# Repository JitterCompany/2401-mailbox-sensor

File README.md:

# Prototype voor brievenbus sensor

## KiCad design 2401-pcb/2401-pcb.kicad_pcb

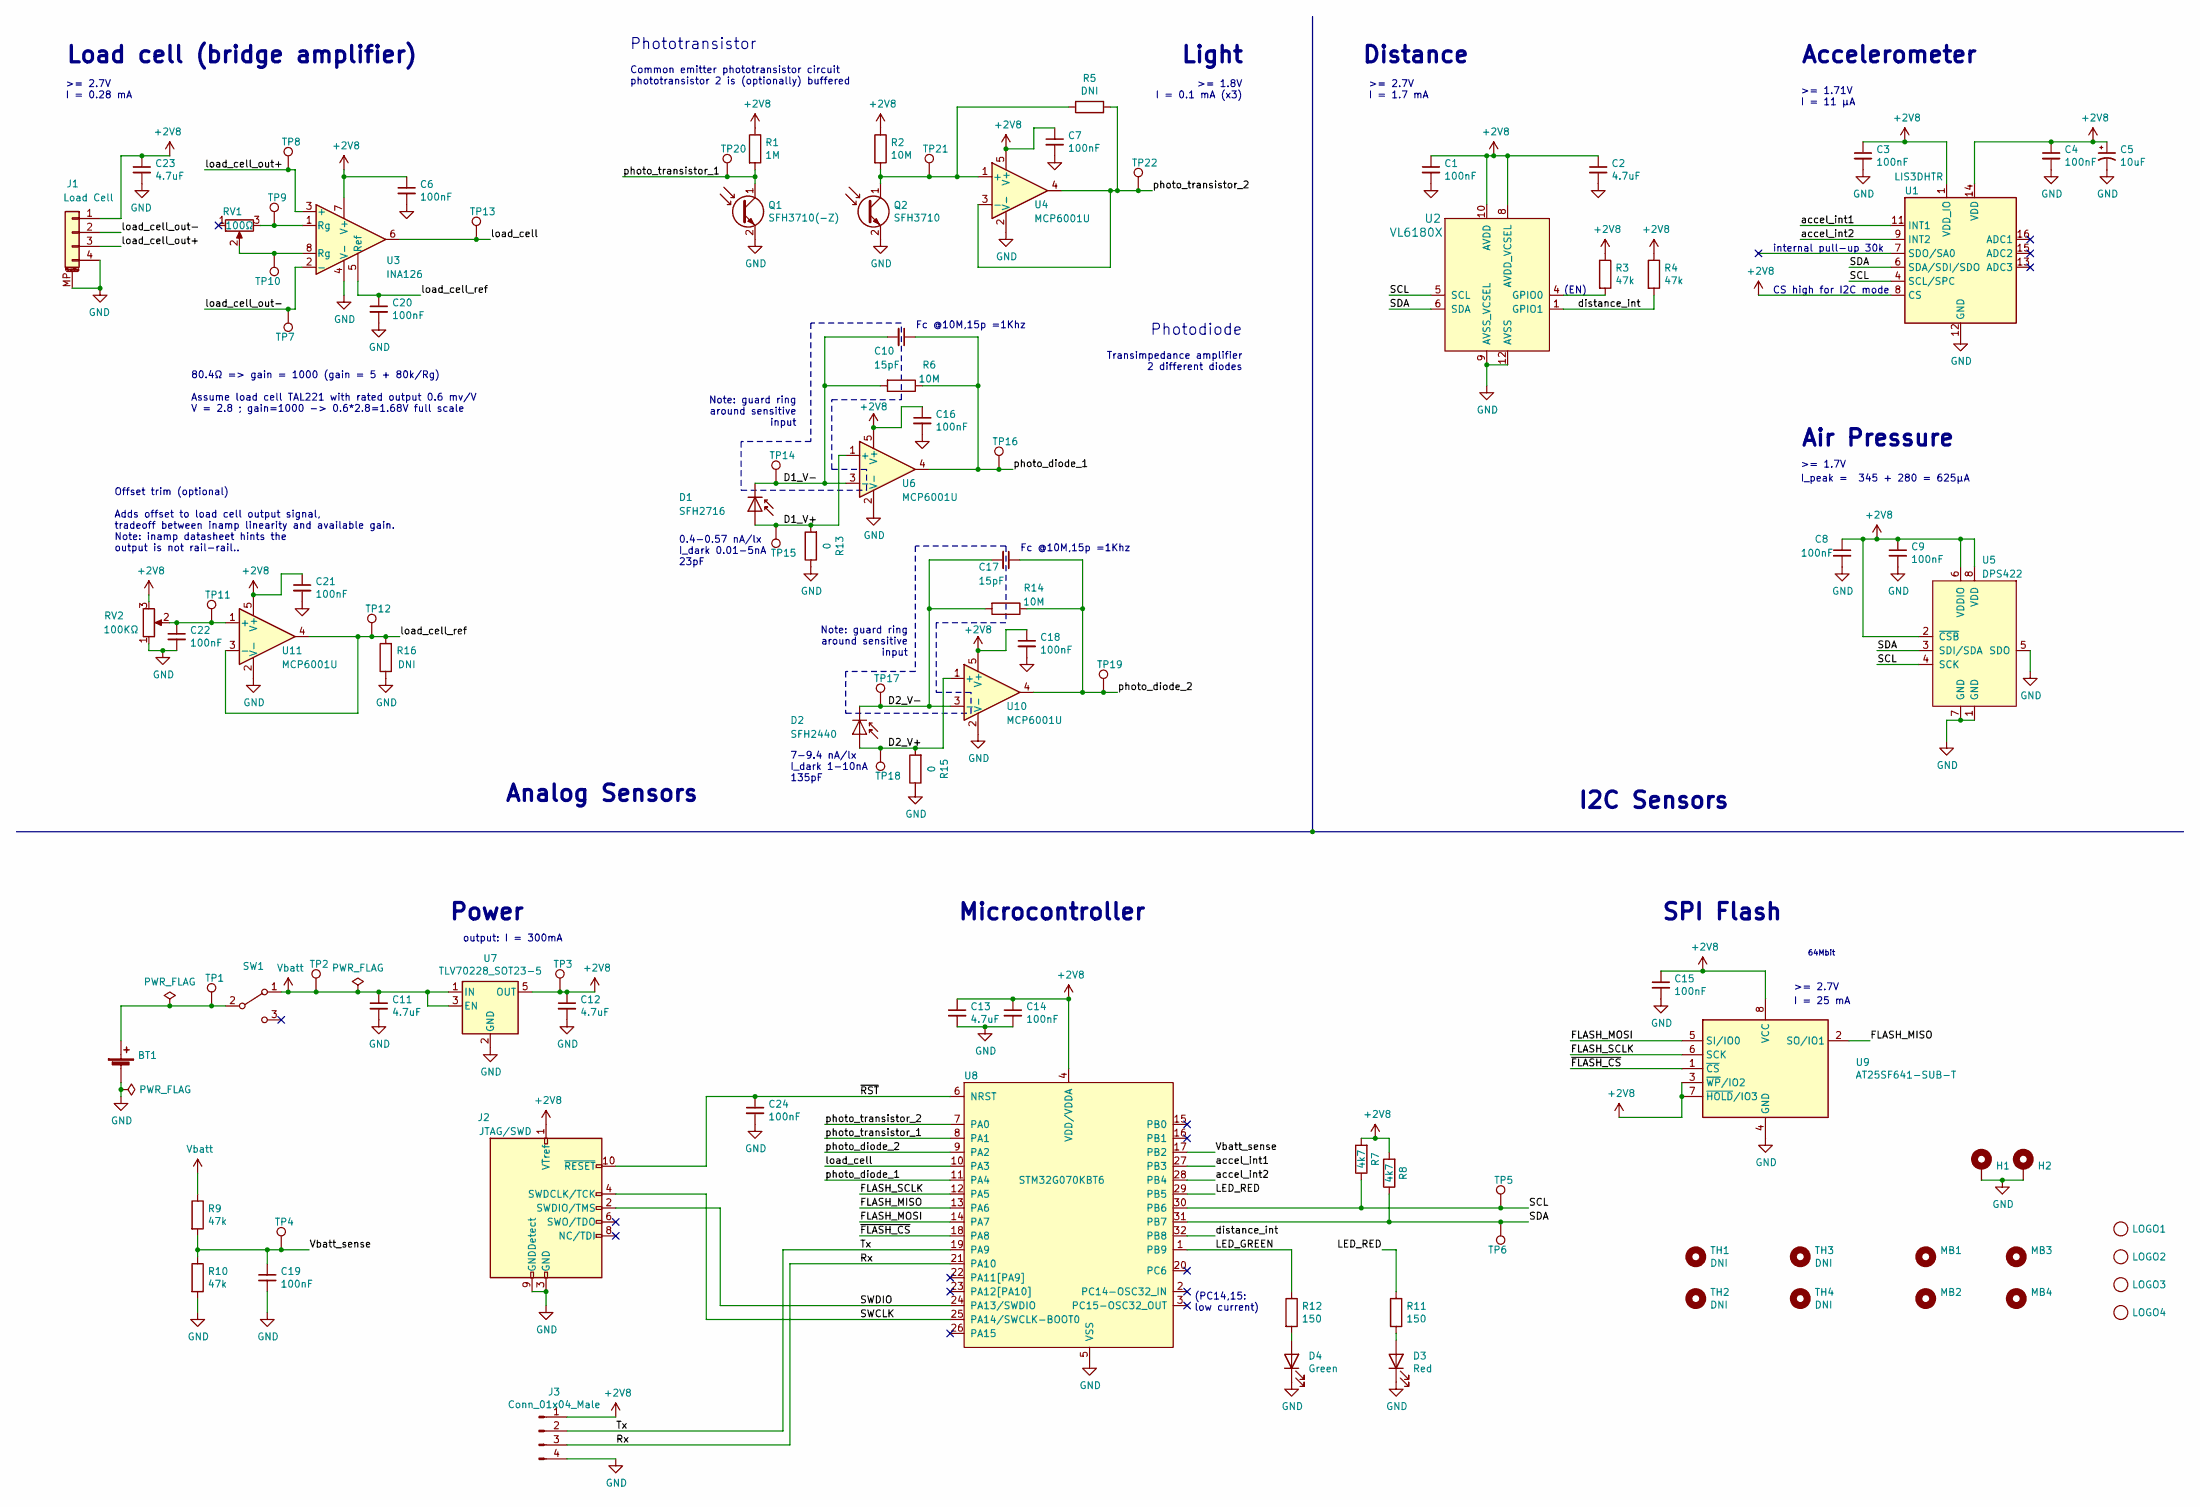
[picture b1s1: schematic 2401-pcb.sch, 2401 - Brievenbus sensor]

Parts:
BT1: SMTU 2450N-1-LF; BatteryHolder_SMTU-2450N-1-LF_1x2450; MPN SMTU 2450N-1-LF; Farnell 1216356
C1, C3, C4, C6, C7, C8, C9, C14, C15, C16, C18, C19, C20, C21, C22, C24: 100nF; C_0603_1608Metric
C2, C11, C12, C13, C23: 4.7uF; C_0805_2012Metric
C5: 10uF; CP_Elec_4x5.4; MPN MCVKZ035M100DA1L; Farnell 2611336
C10, C17: 15pF; C_0603_1608Metric
D1: SFH2716; D_0805_2012Metric; MPN SFH 2716; Farnell 2981722
D2: SFH2440; Osram_SMD-DIL2_4.5x4.0mm; MPN SFH 2440; Farnell 2981709
D3: Red; LED_0805_2012Metric; MPN KPT-2012EC; Farnell 2099236
D4: Green; LED_0805_2012Metric; MPN KP-2012LSGC; Farnell 2463991
H1, H2: DNI; MountingHole_4.5mm_Pad_Via
J1: Load Cell; JST_PH_S4B-PH-SM4-TB_1x04-1MP_P2.00mm_Horizontal; MPN S4B-PH-SM4-TB(LF)(SN); Farnell 9492631
J2: JTAG/SWD; connector_jtag_10pin_shrouded; MPN 20021521-00010T1LF
J3: Conn_01x04_Male; PinHeader_1x04_P2.54mm_Vertical
LOGO1, LOGO3: DNI; Jitter
LOGO2, LOGO4: DNI; Symbol_Jitter-Icon_CopperAndSilkScreenTop
MB1, MB2, MB3, MB4: DNI; MouseBite_3.5mmx2.2mm_breakaway
Q1: SFH3710(-Z); D_0805_2012Metric_Pad1.15x1.40mm_HandSolder; MPN SFH3710-Z; Farnell 2981749
Q2: SFH3710; D_0805_2012Metric_Pad1.15x1.40mm_HandSolder; MPN SFH3710; Farnell 1573490
R1: 1M; R_0805_2012Metric_Pad1.15x1.40mm_HandSolder
R2, R6, R14: 10M; R_0805_2012Metric_Pad1.15x1.40mm_HandSolder
R3, R4, R9, R10: 47k; R_0805_2012Metric_Pad1.15x1.40mm_HandSolder
R5, R16: DNI; R_0805_2012Metric_Pad1.15x1.40mm_HandSolder
R7, R8: 4k7; R_0805_2012Metric_Pad1.15x1.40mm_HandSolder
R11, R12: 150; R_0805_2012Metric_Pad1.15x1.40mm_HandSolder
R13, R15: 0; R_0805_2012Metric_Pad1.15x1.40mm_HandSolder
RV1: 100Ω; Potentiometer_Bourns_3314J_Vertical; MPN 3314J-2-101E; Farnell 2328505
RV2: 100KΩ; Potentiometer_Bourns_3314J_Vertical; MPN 3314J-2-104E; Farnell 2328506
SW1: SW_SPDT; slide_switch_09.03201.02; MPN 09.03201.02; Farnell 1608080
TH1, TH2, TH3, TH4: DNI; Tooling_hole_4.1mm_aisler
TP1, TP2, TP3, TP4, TP5, TP6, TP7, TP8, TP9, TP10, TP11, TP12, TP13, TP15, TP16, TP18, TP19, TP20, TP21, TP22: DNI; TestPoint_THTPad_D1.0mm_Drill0.5mm
TP14, TP17: DNI; TestPoint_Pad_D1.0mm
U1: LIS3DHTR; LGA-16_3x3mm_P0.5mm_LayoutBorder3x5y; MPN LIS3DHTR; Mouser 511-LIS3DHTR
U2: VL6180X; MPN VL6180XV0NR/1; Farnell 2462820
U3: INA126; VSSOP-8_3.0x3.0mm_P0.65mm; MPN INA126E; Farnell 3004490
U4, U6, U10, U11: MCP6001U; SOT-23-5; MPN MCP6001U; Farnell 8540845
U5: DPS422; Bosch_LGA-8_2x2.5mm_P0.65mm_ClockwisePinNumbering; MPN DPS422XTSA1; Farnell 2986299
U7: TLV70228_SOT23-5; SOT-23-5; MPN TLV70228DBVT; Farnell 2492371
U8: STM32G070KBT6; LQFP-32_7x7mm_P0.8mm; MPN STM32G070KBT6; Mouser 511-STM32G070KBT6
U9: AT25SF641-SUB-T; SOIC-8_5.275x5.275mm_P1.27mm; MPN AT25SF641-SUB-T; Farnell 2988514

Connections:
+2V8: C1.1, C2.1, C3.1, C4.1, C5.1, C6.1, C7.1, C8.1, C9.1, C12.1, C13.1, C14.1, C15.1, C16.1, C18.1, C21.1, C23.1, J1.1, J2.1 (VTref), J3.1, R1.1, R2.1, R3.1, R4.1, R7.2, R8.2, RV2.3, TP3.1, U1.1 (VDD_IO), U1.8 (CS), U1.14 (VDD), U2.8 (AVDD_VCSEL), U2.10 (AVDD), U3.7 (V+), U4.5 (V+), U5.2 (~CSB), U5.6 (VDDIO), U5.8 (VDD), U6.5 (V+), U7.5 (OUT), U8.4 (VDD/VDDA), U9.3 (~WP~/IO2), U9.7 (~HOLD~/IO3), U9.8 (VCC), U10.5 (V+), U11.5 (V+)
/D1_V+: D1.2 (A), R13.2, TP15.1, U6.1 (+)
/D1_V-: C10.2, D1.1 (K), R6.2, TP14.1, U6.3 (-)
/D2_V+: D2.2 (A), R15.2, TP18.1, U10.1 (+)
/D2_V-: C17.2, D2.1 (K), R14.2, TP17.1, U10.3 (-)
/FLASH_MISO: U8.13 (PA6), U9.2 (SO/IO1)
/FLASH_MOSI: U8.14 (PA7), U9.5 (SI/IO0)
/FLASH_SCLK: U8.12 (PA5), U9.6 (SCK)
/LED_GREEN: R12.1, U8.1 (PB9)
/LED_RED: R11.1, U8.29 (PB5)
/Rx: J3.3, U8.21 (PA10)
/SCL: R7.1, TP5.1, U1.4 (SCL/SPC), U2.5 (SCL), U5.4 (SCK), U8.30 (PB6)
/SDA: R8.1, TP6.1, U1.6 (SDA/SDI/SDO), U2.6 (SDA), U5.3 (SDI/SDA), U8.31 (PB7)
/SWCLK: J2.4 (SWDCLK/TCK), U8.25 (PA14/SWCLK-BOOT0)
/SWDIO: J2.2 (SWDIO/TMS), U8.24 (PA13/SWDIO)
/Tx: J3.2, U8.19 (PA9)
/Vbatt_sense: C19.1, R9.2, R10.1, TP4.1, U8.17 (PB2)
/accel_int1: U1.11 (INT1), U8.27 (PB3)
/accel_int2: U1.9 (INT2), U8.28 (PB4)
/distance_int: R4.2, U2.1 (GPIO1), U8.32 (PB8)
/load_cell: TP13.1, U3.6, U8.10 (PA3)
/load_cell_out+: J1.3, TP8.1, U3.3 (+)
/load_cell_out-: J1.2, TP7.1, U3.2 (-)
/load_cell_ref: C20.1, R16.2, TP12.1, U3.5 (Ref), U11.3 (-), U11.4
/photo_diode_1: C10.1, R6.1, TP16.1, U6.4, U8.11 (PA4)
/photo_diode_2: C17.1, R14.1, TP19.1, U8.9 (PA2), U10.4
/photo_transistor_1: Q1.1 (C), R1.2, TP20.1, U8.8 (PA1)
/photo_transistor_2: R5.1, TP22.1, U4.3 (-), U4.4, U8.7 (PA0)
/~FLASH_CS: U8.18 (PA8), U9.1 (~CS)
/~RST: C24.1, J2.10 (~RESET~), U8.6 (NRST)
GND: BT1.2 (-), C1.2, C2.2, C3.2, C4.2, C5.2, C6.2, C7.2, C8.2, C9.2, C11.2, C12.2, C13.2, C14.2, C15.2, C16.2, C18.2, C19.2, C20.2, C21.2, C22.2, C23.2, C24.2, D3.1 (K), D4.1 (K), H1.1, H2.1, J1.4, J1.MP (MountPin), J2.3 (GND), J2.5 (GND), J2.9 (GNDDetect), J3.4, Q1.2 (E), Q2.2 (E), R10.2, R13.1, R15.1, R16.1, RV2.1, U1.5 (GND), U1.10 (GND), U1.12 (GND), U2.9 (AVSS_VCSEL), U2.12 (AVSS), U3.4 (V-), U4.2 (V-), U5.1 (GND), U5.5 (SDO), U5.7 (GND), U6.2 (V-), U7.2 (GND), U8.5 (VSS), U9.4 (GND), U10.2 (V-), U11.2 (V-)
unnamed: BT1.1 (+), SW1.2 (B), TP1.1
unnamed: C22.1, RV2.2, TP11.1, U11.1 (+)
unnamed: D3.2 (A), R11.2
unnamed: D4.2 (A), R12.2
unnamed: Q2.1 (C), R2.2, R5.2, TP21.1, U4.1 (+)
unnamed: R3.2, U2.4 (GPIO0)
unnamed: RV1.2, TP10.1, U3.8 (Rg)
unnamed: RV1.3, TP9.1, U3.1 (Rg)
Vbatt: C11.1, R9.1, SW1.1 (A), TP2.1, U7.1 (IN), U7.3 (EN)

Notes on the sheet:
SPI Flash
64Mbit
>= 2.7V
I = 25 mA
Power
output: I = 300mA
Microcontroller
(PC14,15: low current)
(EN)
I2C Sensors
>= 2.7V I = 1.7 mA
Distance
Load cell (bridge amplifier)
80.4Ω => gain = 1000 (gain = 5 + 80k/Rg) Assume load cell TAL221 with rated output 0.6 mv/V V = 2.8 ; gain=1000 -> 0.6*2.8=1.68V full scale
Offset trim (optional) Adds offset to load cell output signal, tradeoff between inamp linearity and available gain. Note: inamp datasheet hints the output is not rail-rail..
>= 2.7V I = 0.28 mA
Light
Phototransistor
Photodiode
Common emitter phototransistor circuit phototransistor 2 is (optionally) buffered
Analog Sensors
7-9.4 nA/lx I_dark 1-10nA 135pF
0.4-0.57 nA/lx I_dark 0.01-5nA 23pF
Fc @10M,15p =1Khz
Transimpedance amplifier 2 different diodes
>= 1.8V I = 0.1 mA (x3)
Note: guard ring around sensitive input
Accelerometer
internal pull-up 30k
CS high for I2C mode
>= 1.71V I = 11 µA
I_peak = 345 + 280 = 625µA
>= 1.7V
Air Pressure

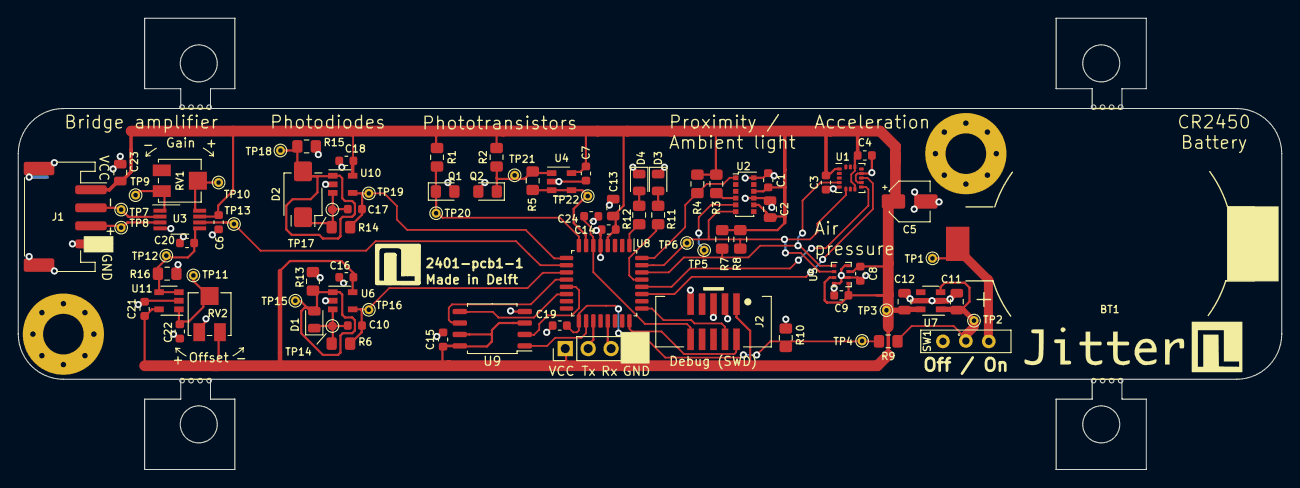
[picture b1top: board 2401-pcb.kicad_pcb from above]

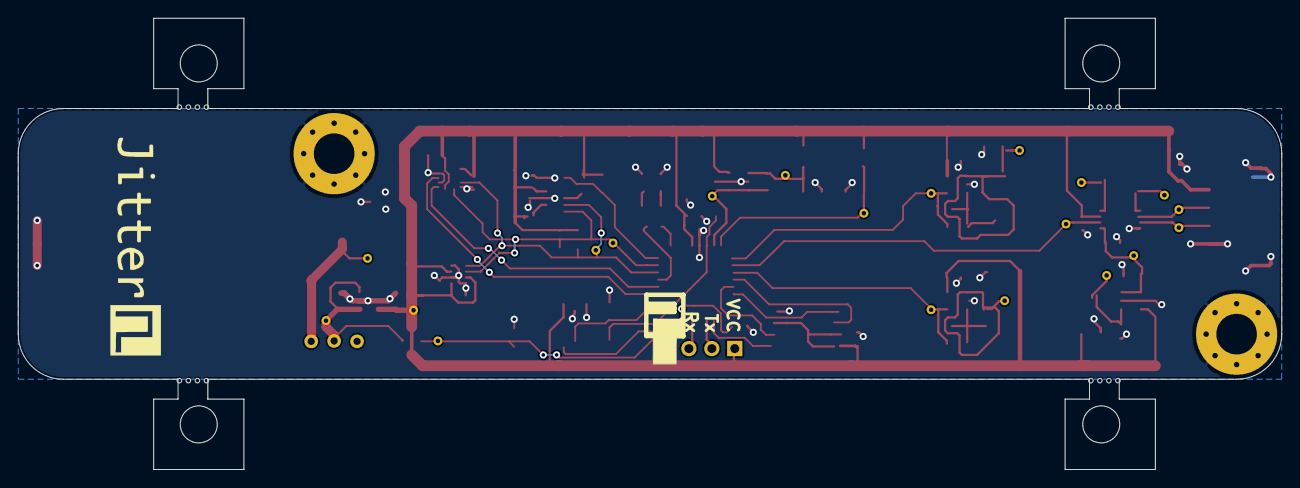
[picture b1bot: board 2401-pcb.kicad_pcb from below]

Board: 2 copper layers, 140.0 x 50.0 mm, 100 parts (2 on the bottom side), 40 nets.

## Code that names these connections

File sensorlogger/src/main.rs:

#![deny(unsafe_code)]
#![no_main]
#![no_std]

extern crate cortex_m;
extern crate cortex_m_rt as rt;
extern crate panic_halt;

use rt::entry;
use core::fmt::Write;

use stm32g0xx_hal::{
    prelude::*,
    stm32,
    serial::Config,
    i2c,
    spi,
    analog::adc::{Precision, SampleTime},
};

use spi_memory::series25::Flash;

use dps422::{DPS422, self};
use vl6180x::{VL6180X};
use lis3dh::{Lis3dh, accelerometer::Accelerometer};

use shared_bus;

mod log_storage;
use log_storage::StorageEngine;

use embedded_hal::digital::v2::OutputPin;

mod sensors;
use sensors::SensorData;


#[entry]
fn main() -> ! {
    let dp = stm32::Peripherals::take().expect("cannot take peripherals");
    let mut rcc = dp.RCC.constrain();
    let gpiob = dp.GPIOB.split(&mut rcc);
    let mut led1 = gpiob.pb5.into_push_pull_output();
    // led1.set_high().unwrap();

    let mut led2 = gpiob.pb9.into_push_pull_output();
    led2.set_low().unwrap();

    // Get the delay provider.
    let cp = cortex_m::Peripherals::take().unwrap();
    let mut delay = cp.SYST.delay(&mut rcc);

    let gpioa = dp.GPIOA.split(&mut rcc);


    let tx = gpioa.pa9;
    let rx = gpioa.pa10;
    let mut usart = dp
        .USART1
        .usart(tx, rx, Config::default().baudrate(500000.bps()), &mut rcc)
        .unwrap();

    writeln!(usart, "Hallo, brievenbus!\n").unwrap();


    let spi = {

        let sck = gpioa.pa5;
        let miso = gpioa.pa6;
        let mosi = gpioa.pa7;
        dp.SPI1.spi(
            (sck, miso, mosi),
            spi::MODE_0,
            1000.khz(),
            &mut rcc)
    };

    let mut flash_cs = gpioa.pa8.into_push_pull_output();
    flash_cs.set_high().unwrap();
    let mut flash = Flash::init(spi, flash_cs).unwrap();
    let id = flash.read_jedec_id().unwrap();
    let flash_size = 0x800000;
    let mut storage = StorageEngine::new(flash, flash_size, 0x1000, 0x100);
    let offset = storage.init().unwrap();

    writeln!(usart, "Init flash with id: {:?}, offset: {}\n", id, offset  / (SensorData::size() + 1)).unwrap();


    // storage.erase(0).unwrap();
    // storage.erase(1).unwrap();

    #[cfg(feature = "use_flash")]
    {
        let mut i = 0u32;
        let n  = flash_size / (SensorData::size() + 1);
        while i < n {
            match storage.read_sensors(i) {
                Ok(s) => {
                    #[allow(unsafe_code)]
                    unsafe {
                        writeln!(usart, "{:.1},{:.1},{},{},{},{},{},{},{},{},{}",
                            s.pressure,
                            s.temp,
                            s.accel_x,
                            s.accel_y,
                            s.accel_z,
                            s.photo_t1,
                            s.photo_t2,
                            s.photo_d1,
                            s.photo_d2,
                            s.vbat,
                            s.distance
                        ).unwrap();

                        writeln!(usart, "plot {},{},{},{}",
                            s.photo_t1,
                            s.photo_t2,
                            s.photo_d1,
                            s.photo_d2,
                        ).unwrap();
                    }
                    // writeln!(usart, "{:?}", s).unwrap()
                },
                Err(_err) => break,
            };
            i += 1;
        }
        writeln!(usart, "Mem dump done").unwrap();
    }


    let mut adc = dp.ADC.constrain(&mut rcc);
    adc.set_sample_time(SampleTime::T_2);
    adc.set_precision(Precision::B_12);

    // photo transistor 1 = PA1
    // photo transistor 2 = PA0
    // photo diode 1 =      PA4
    // photo diode 2 =      PA2
    let mut phototransistor2_pin = gpioa.pa0.into_analog();
    let mut phototransistor1_pin = gpioa.pa1.into_analog();
    let mut photodiode1_pin = gpioa.pa4.into_analog();
    let mut photodiode2_pin = gpioa.pa2.into_analog();

    let mut vbat_pin = gpiob.pb2.into_analog();


    // I2C pins
    let scl = gpiob.pb6.into_open_drain_output();
    let sda = gpiob.pb7.into_open_drain_output();

    let i2c = dp
        .I2C1
        .i2c(sda, scl, i2c::Config::with_timing(0x2020151b), &mut rcc);

    writeln!(usart, "i2c initialized!\n").unwrap();

    let manager = shared_bus::CortexMBusManager::new(i2c);

    let mut dps = DPS422::new(manager.acquire(), 0x76, &dps422::Config::new().pres_rate(dps422::PressureRate::_128_SPS)).expect("dps422 failed to intialize");

    writeln!(usart, "DPS422 init done").unwrap();

    let mut vl6180x = VL6180X::new(manager.acquire()).expect("vl6180x failed to intialize");
    writeln!(usart, "VL6180X init done..\n").unwrap();

    let mut lis3dh = Lis3dh::new(manager.acquire(), 0x19).unwrap();
    lis3dh.set_range(lis3dh::Range::G2).unwrap();
    writeln!(usart, "Lis3dh init done..\n").unwrap();

    lis3dh.set_range(lis3dh::Range::G8).unwrap();

    dps.trigger_measurement(true, true, false).unwrap();
    vl6180x.start_ranging().unwrap();
    let mut sensordata = SensorData::new();
    loop {
        // led2.toggle().unwrap();

        if dps.data_ready().unwrap() {
            let pressure = dps.read_pressure_calibrated().unwrap();
            let temp = dps.read_temp_calibrated().unwrap();
            // writeln!(usart, "pressure: {:.1} [kPa]\t temp: {:.1} [˚C]", pressure, temp).unwrap();
            dps.trigger_measurement(true, true, false).unwrap();
            sensordata.pressure(pressure);
            sensordata.temp(temp);
        }

        let status = vl6180x.int_status().unwrap();
        if (status & 0b100) == 0b100 {
            let range = vl6180x.read_range().unwrap();
            // writeln!(usart, "range = {} [mm]\n", range).unwrap();
            vl6180x.clear_int().unwrap();
            vl6180x.start_ranging().unwrap();
            sensordata.distance(range);
        }

        let accel = lis3dh.acceleration().unwrap();
        // writeln!(usart, "accel = {}, {}, {}", accel.x, accel.y, accel.z).unwrap();
        sensordata.accel_x(accel.x);
        sensordata.accel_y(accel.y);
        sensordata.accel_z(accel.z);

        let pt1: u16 = adc.read(&mut phototransistor1_pin).expect("adc read failed");
        let pt2: u16 = adc.read(&mut phototransistor2_pin).expect("adc read failed");
        let pd1: u16 = adc.read(&mut photodiode1_pin).expect("adc read failed");
        let pd2: u16 = adc.read(&mut photodiode2_pin).expect("adc read failed");
        sensordata.photo_t1(pt1);
        sensordata.photo_t2(pt2);
        sensordata.photo_d1(pd1);
        sensordata.photo_d2(pd2);

        let vbat: u16 = adc.read(&mut vbat_pin).expect("adc read failed");
        sensordata.vbat(vbat);

        // writeln!(usart, "photo transistors: {},  {}", pt1, pt2).unwrap();
        // writeln!(usart, "photo diodes: {},  {}", pd1, pd2).unwrap();
        // writeln!(usart, "vbat: {} mV?", vbat*2*3000/4096).unwrap();

        if sensordata.ready() {
            // writeln!(usart, "{:?}", sensordata).unwrap();
            #[allow(unsafe_code)]
            unsafe {
                let s = sensordata;
                writeln!(usart, "plot {},{}",
                    // s.distance,
                    // s.temp
                    s.photo_t1,
                    s.photo_t2,
                    // s.photo_d1,
                    // s.photo_d2,
                ).unwrap();
            }
            // led1.set_high().unwrap();

            #[cfg(feature = "use_flash")]
            match storage.write(sensordata) {
                Err(err) => writeln!(usart, "error while writing to flash: {:?}", err).unwrap(),
                _ => {}
            };

            // led1.set_low().unwrap();
            sensordata = SensorData::new();
        } else {
            writeln!(usart, "sensors not ready yet..").unwrap();
        }

        delay.delay_ms(400_u16);

    }
}

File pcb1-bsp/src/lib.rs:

#![no_std]

// examples: https://github.com/rubberduck203/stm32f3-discovery
// https://github.com/nrf-rs/nrf52-hal

pub use switch_hal;
use switch_hal::{ActiveHigh, Switch, IntoSwitch, OutputSwitch};

use stm32g0xx_hal::{
    prelude::*,
    stm32,
    gpio::gpiob,
    gpio::{Output, PushPull},
};


type RedLed = Switch<gpiob::PB5<Output<PushPull>>, ActiveHigh>;
type GreenLed = Switch<gpiob::PB9<Output<PushPull>>, ActiveHigh>;

pub struct Leds {
    pub led_red: RedLed,
    pub led_green: GreenLed
}

impl Leds {

    /// Initializes the user LEDs to OFF
    pub fn new(pb5: RedLed, pb9: GreenLed) -> Self {
        Self {
            led_red: pb5,
            led_green: pb9
        }
    }

}


pub struct Board {
    pub leds: Leds
}

impl Board {

    pub fn new() -> Self {

        let dp = stm32::Peripherals::take().expect("cannot take peripherals");
        let mut rcc = dp.RCC.constrain();
        let gpiob = dp.GPIOB.split(&mut rcc);
        let pb5 = gpiob.pb5.into_push_pull_output().into_active_high_switch();
        let pb9 = gpiob.pb9.into_push_pull_output().into_active_high_switch();

        let mut leds = Leds::new(pb5, pb9);
        leds.led_green.off().ok();
        leds.led_red.off().ok();

        Board {leds}
    }
}

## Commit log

2020-01-17 Add pcb directory (WIP)
2020-01-27 Improve schematics
2020-01-27 Schematics: finish photodiode circuit
    The design calculations are in the xls file.
2020-01-27 PCB: assign/fix footprints + 3D
2020-01-28 PCB: routing is more or less done
    The KiCAD DRC passes, but it is not checked againts the Jitter
    Checklist..
2020-01-29 Add pinmapping sheet
2020-01-29 Schematics: reorder to similar layout as PCB
2020-01-29 Update pinmapping sheet from schematics
2020-01-29 Schematics: remap LED pins: PC13-15 are low-current only
2020-01-29 PCB: schematics & layout complete [Checklist PASS]
2020-01-30 PCB/Schematic bugfix: add NRST capacitor, update air pressure symbol
2020-01-30 Schematics: don't reference rescue library
2020-01-30 Add jitter schematic template to repo
2020-02-05 PCB: export V1 layout
2020-02-10 PCB: add Final production BOM
2020-02-10 PCB: last BOM update before ordering
2020-03-14 Add blinky project for pcb1
2020-03-14 Try to create a board support crate
2020-03-14 Create blinky example using BSP
2020-03-18 Add peripheral verification firmware
    tests for i2c and spi devices.
2020-05-12 Start sensorlogger firmware using shared-bus (for sharing i2c)
2020-05-12 Add vl6180 and lis3dh i2c sensors to sensorlogger
2020-05-12 Add adc sensors
2020-05-12 Remove VTemp internal temperature sensor as it is unnecessary
2020-05-19 Start with spi log storage engine. Syntax is ok now.
2020-05-20 add flash init params and do some cleanup
2020-05-20 basic storage engine is working
    Write packets with prefix. Search for prefix bytes at fixed offsets to
    find next address for writing (after reset).
    Edge cases not handled yet. Such as writing accross page boundaries.
2020-05-22 Small benchmark shows that writing fails after first block of 256 bytes
    The flash automatically wraps to the first byte of the current page. so
    we need to make sure we do not cross that boundary and issue a new write
    command for the remaining bytes.
2020-05-22 Implement writing accross page boundaries
2020-05-22 Implement custom error type with from trait implemented
2020-05-23 Implement reading sensor data from spi memory
2020-05-24 Fix i2c issues with newest stm32g0xx-hal version
2020-05-24 Add release profile
2020-05-24 Handle flash full error; print message on uart.
    Also turn on led1 while writing to flash to indicate to not turn off the
    board.
2020-05-25 Output logdata as csv
2020-05-29 Add use_flash feature to toggle on/off spi flash during compile time
2020-06-01 Update hal lib
2020-06-02 Add Brievenbusetector firmware with first detection algorithm
2020-06-02 Implement correcting adc for current vdd value
2020-06-03 Use ptr::read_volatile to read VREFINT calibration value
2020-06-08 Add panc handler with blink and fix sensor size
    bool = 1 byte
2020-06-11 PCb changes
2020-06-11 Changes for production at aisler
2020-06-15 Add analysis notebook
2020-06-15 Dump memory first before initializing storage engine
    It can take very long to find the next index if the memory is quite
    full.
2020-06-16 Update notebook
2020-06-16 Add new triggered state before ranging
    also refactor main code a bit into mire state machine like. Add detector
    object for averaging.
2020-06-18 Improve flow of code to prevent unnecessary delays
    When triggered we don't want delays that can make us miss the detection.
2020-06-22 Update analysis
